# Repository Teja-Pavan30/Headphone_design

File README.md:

# Headphone_design
pcb design of head phone and CAD
working to make the signal integrity better and going to 4 layer board

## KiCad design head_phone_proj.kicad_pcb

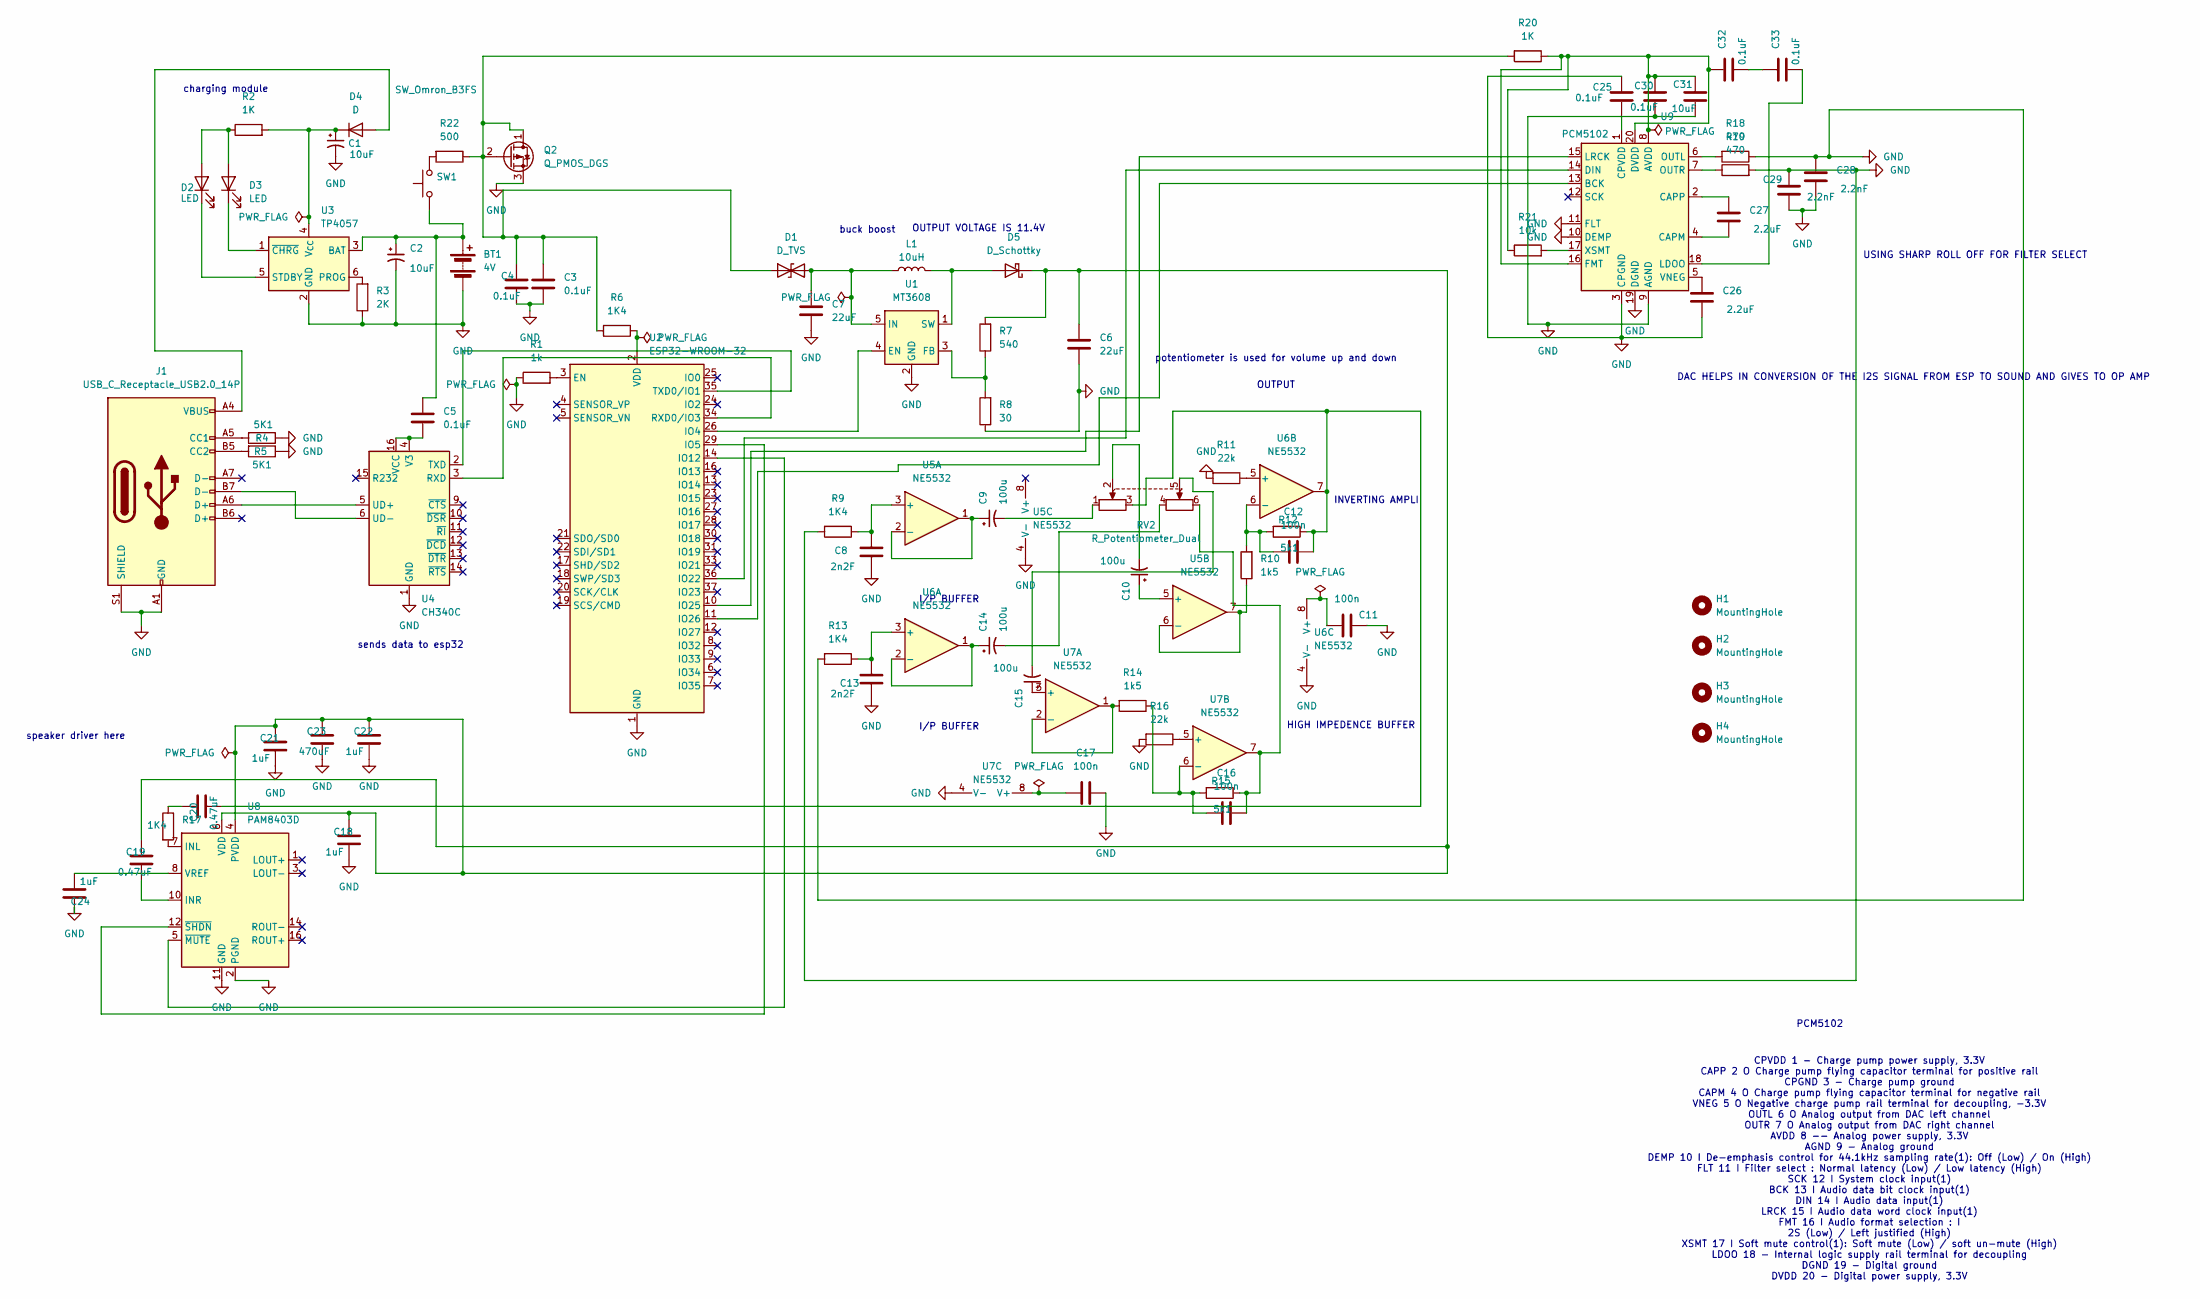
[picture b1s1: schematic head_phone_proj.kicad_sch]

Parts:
BT1: 4V; BatteryHolder_Seiko_MS621F
C1, C2: 10uF; CP_Elec_5x5.3
C3, C4, C5, C25, C30, C32, C33: 0.1uF; C_0805_2012Metric_Pad1.18x1.45mm_HandSolder
C6, C7: 22uF; C_0402_1005Metric_Pad0.74x0.62mm_HandSolder
C8, C13: 2n2F; C_0805_2012Metric_Pad1.18x1.45mm_HandSolder
C9, C10, C14, C15: 100u; CP_Elec_5x5.3
C11, C12, C16, C17: 100n; C_0805_2012Metric_Pad1.18x1.45mm_HandSolder
C18, C21, C22, C24: 1uF; C_0805_2012Metric_Pad1.18x1.45mm_HandSolder
C19, C20: 0.47uF; C_0805_2012Metric_Pad1.18x1.45mm_HandSolder
C23: 470uF; C_0805_2012Metric_Pad1.18x1.45mm_HandSolder
C26, C27: 2.2uF; C_0805_2012Metric_Pad1.18x1.45mm_HandSolder
C28, C29: 2.2nF; C_0805_2012Metric_Pad1.18x1.45mm_HandSolder
C31: 10uF; C_0805_2012Metric_Pad1.18x1.45mm_HandSolder
D1: D_TVS; D_0603_1608Metric_Pad1.05x0.95mm_HandSolder
D2, D3: LED; LED_0603_1608Metric_Pad1.05x0.95mm_HandSolder
D4: D; D_0603_1608Metric_Pad1.05x0.95mm_HandSolder
D5: D_Schottky; D_0603_1608Metric_Pad1.05x0.95mm_HandSolder
H1, H2, H3, H4: MountingHole; MountingHole_2.2mm_M2
J1: USB_C_Receptacle_USB2.0_14P; USB_C_Receptacle_HRO_TYPE-C-31-M-12
L1: 10uH; L_0603_1608Metric_Pad1.05x0.95mm_HandSolder
Q2: Q_PMOS_DGS; SOT-23W_Handsoldering
R1: 1k; R_0603_1608Metric_Pad0.98x0.95mm_HandSolder
R2, R20: 1K; R_0603_1608Metric_Pad0.98x0.95mm_HandSolder
R3: 2K; R_0603_1608Metric_Pad0.98x0.95mm_HandSolder
R4, R5: 5K1; R_0603_1608Metric_Pad0.98x0.95mm_HandSolder
R6, R9, R13, R17: 1K4; R_0603_1608Metric_Pad0.98x0.95mm_HandSolder
R7: 540; R_0603_1608Metric_Pad0.98x0.95mm_HandSolder
R8: 30; R_0603_1608Metric_Pad0.98x0.95mm_HandSolder
R10, R14: 1k5; R_0603_1608Metric_Pad0.98x0.95mm_HandSolder
R11, R16: 22k; R_0603_1608Metric_Pad0.98x0.95mm_HandSolder
R12, R15: 5k1; R_0603_1608Metric_Pad0.98x0.95mm_HandSolder
R18, R19: 470; R_0603_1608Metric_Pad0.98x0.95mm_HandSolder
R21: 10k; R_0603_1608Metric_Pad0.98x0.95mm_HandSolder
R22: 500; R_0603_1608Metric_Pad0.98x0.95mm_HandSolder
RV2: R_Potentiometer_Dual; Potentiometer_Alpha_RD902F-40-00D_Dual_Vertical
SW1: SW_Omron_B3FS; SW_SPST_Omron_B3FS-100xP
U1: MT3608; SOT-23-6
U2: ESP32-WROOM-32
U3: TP4057; TSOT-23-6_HandSoldering
U4: CH340C; SOIC-16_3.9x9.9mm_P1.27mm
U5, U6, U7: NE5532; DIP-8_W7.62mm_Socket
U8: PAM8403D; SOP-16_3.9x9.9mm_P1.27mm
U9: PCM5102; TSSOP-20_4.4x6.5mm_P0.65mm

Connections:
GND: BT1.2 (-), C1.2, C2.2, C3.2, C4.2, C6.2, C7.2, C8.2, C11.2, C13.2, C17.2, C18.2, C21.2, C22.2, C23.2, C24.1, C25.1, C26.2, C28.1, C28.2, C29.1, C29.2, C30.2, C31.2, J1.A1 (GND), J1.A12 (GND), J1.B1 (GND), J1.B12 (GND), J1.S1 (SHIELD), Q2.3 (S), R1.1, R3.1, R4.1, R5.1, R8.1, R9.2, R11.2, R13.2, R16.2, R18.1, R19.2, U1.2 (GND), U2.1 (GND), U2.15 (GND), U2.38 (GND), U2.39 (GND), U3.2 (GND), U4.1 (GND), U5.4 (V-), U6.4 (V-), U7.4 (V-), U8.2 (PGND), U8.11 (GND), U8.15 (PGND), U9.3 (CPGND), U9.9 (AGND), U9.10 (DEMP), U9.11 (FLT), U9.19 (DGND)
unnamed: BT1.1 (+), C2.1, C5.1, SW1.1, U3.3 (BAT)
unnamed: C9.2, RV2.1
unnamed: C10.2, RV2.2
unnamed: C12.2, C20.2, R12.1, RV2.3, U6.7
unnamed: C14.2, RV2.4
unnamed: C15.2, RV2.5
unnamed: C16.2, R15.1, RV2.6, U7.7
unnamed: C20.1, R17.1
unnamed: C32.2, C33.1
unnamed: C3.1, C4.1, D1.1 (A1), Q2.1 (D), Q2.2 (G), R6.2, R20.2, R22.1
unnamed: C7.1, D1.2 (A2), L1.1, U1.5 (IN)
unnamed: D2.2 (A), D3.2 (A), R2.1
unnamed: D2.1 (K), U3.5 (STDBY)
unnamed: D3.1 (K), U3.1 (~CHRG)
unnamed: D4.2 (A), J1.A4 (VBUS), J1.A9 (VBUS), J1.B4 (VBUS), J1.B9 (VBUS)
unnamed: C1.1, D4.1 (K), R2.2, U3.4 (V_{CC})
unnamed: D5.2 (A), L1.2, U1.1 (SW)
unnamed: C6.1, C18.1, C19.1, C21.1, C22.1, C23.1, D5.1 (K), R7.2, U8.4 (PVDD), U8.6 (VDD), U8.13 (PVDD)
unnamed: J1.A5 (CC1), R4.2
unnamed: J1.B5 (CC2), R5.2
unnamed: R22.2, SW1.2
unnamed: U1.4 (EN), U2.26 (IO4)
unnamed: R7.1, R8.2, U1.3 (FB)
unnamed: R1.2, U2.3 (EN)
unnamed: U2.29 (IO5), U8.12 (~SHDN)
unnamed: U2.14 (IO12), U8.5 (~MUTE)
unnamed: U2.36 (IO22), U9.14 (DIN)
unnamed: U2.10 (IO25), U9.15 (LRCK)
unnamed: U2.11 (IO26), U9.13 (BCK)
unnamed: U2.34 (RXD0/IO3), U4.3 (RXD)
unnamed: U2.35 (TXD0/IO1), U4.2 (TXD)
unnamed: R6.1, U2.2 (VDD)
unnamed: R3.2, U3.6 (PROG)
unnamed: J1.A6 (D+), U4.5 (UD+)
unnamed: J1.B7 (D-), U4.6 (UD-)
unnamed: C5.2, U4.4 (V3), U4.16 (VCC)
unnamed: C8.1, R9.1, U5.3 (+)
unnamed: C9.1, U5.1, U5.2 (-)
unnamed: C10.1, U5.5 (+)
unnamed: R10.1, U5.6 (-), U5.7
unnamed: C13.1, R13.1, U6.3 (+)
unnamed: C14.1, U6.1, U6.2 (-)
unnamed: R11.1, U6.5 (+)
unnamed: C12.1, R10.2, R12.2, U6.6 (-)
unnamed: C11.1, U6.8 (V+)
unnamed: C15.1, U7.3 (+)
unnamed: R14.2, U7.1, U7.2 (-)
unnamed: R16.1, U7.5 (+)
unnamed: C16.1, R14.1, R15.2, U7.6 (-)
unnamed: C17.1, U7.8 (V+)
unnamed: R17.2, U8.7 (INL)
unnamed: C19.2, U8.10 (INR)
unnamed: C24.2, U8.8 (VREF)
unnamed: C30.1, C31.1, C32.1, R20.1, R21.1, U9.8 (AVDD), U9.16 (FMT), U9.20 (DVDD)
unnamed: C27.2, U9.4 (CAPM)
unnamed: C27.1, U9.2 (CAPP)
unnamed: C25.2, U9.1 (CPVDD)
unnamed: C33.2, U9.18 (LDOO)
unnamed: R18.2, U9.6 (OUTL)
unnamed: R19.1, U9.7 (OUTR)
unnamed: C26.1, U9.5 (VNEG)
unnamed: R21.2, U9.17 (XSMT)

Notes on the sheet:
buck boost
speaker driver here
charging module
I/P BUFFER
OUTPUT
USING SHARP ROLL OFF FOR FILTER SELECT
OUTPUT VOLTAGE IS 11.4V
PCM5102
potentiometer is used for volume up and down
CPVDD 1 - Charge pump power supply, 3.3V CAPP 2 O Charge pump flying capacitor terminal for positive rail CPGND 3 - Charge pump ground CAPM 4 O Charge pump flying capacitor terminal for negative rail VNEG 5 O Negative charge pump rail terminal for decoupling, -3.3V OUTL 6 O Analog output from DAC l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
sends data to esp32
DAC HELPS IN CONVERSION OF THE I2S SIGNAL FROM ESP TO SOUND AND GIVES TO OP AMP
INVERTING AMPLI
HIGH IMPEDENCE BUFFER

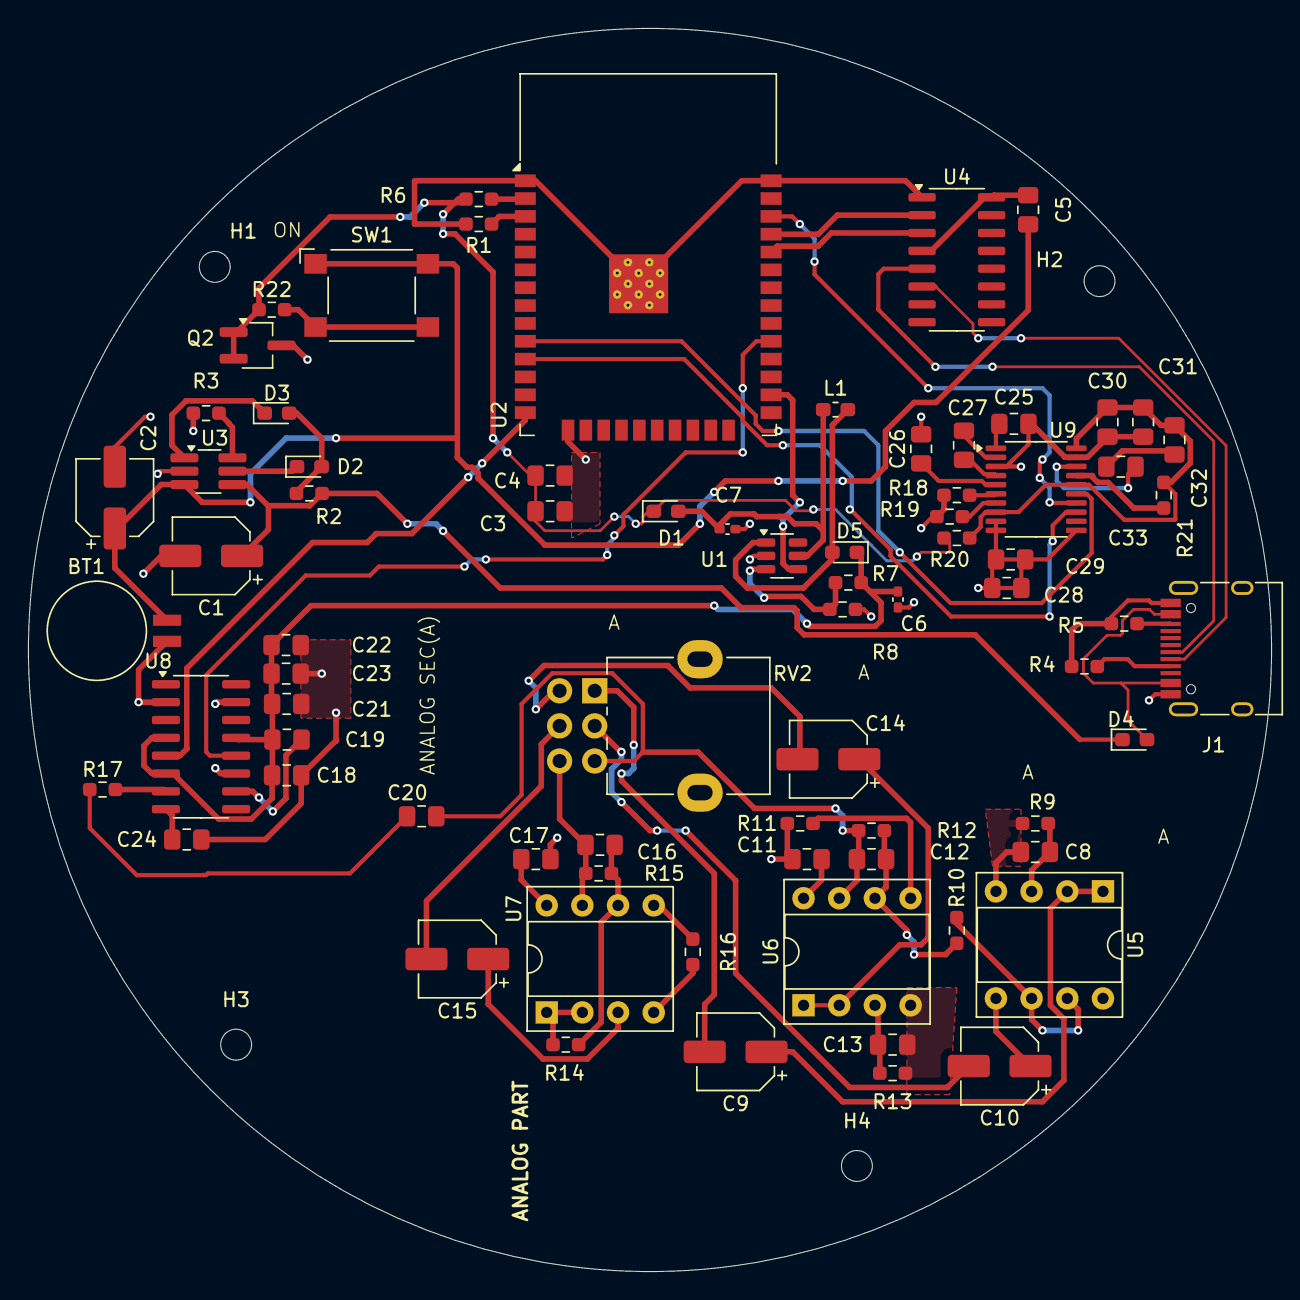
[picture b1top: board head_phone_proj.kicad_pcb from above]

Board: 2 copper layers, 88.5 x 88.5 mm, 79 parts (0 on the bottom side), 63 nets.
